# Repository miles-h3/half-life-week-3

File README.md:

# half-life-week-3
MIDI Keyboard PCB Design inspired by Hack Club's guide: an electronic controller that doesn't make sound on its own but sends the data for a computer/synthesizer to generate that audio. Perhaps it can also be programmed to play audio clips?  

FUNCTION:
One's inherent electrical field interacts with the capacitive keys on the pcb and plays a corresponding sound to the key "pressed." Additionally, the switches above the capacitive keys perform the same function though they havae a more physical response to one's touch.

PCB DESIGN:  

3D PCB MODEL:  

## Bill of Materials (BOM)

| Part | Qty | Unit | Total | Vendor |
| :--- | :---: | :---: | :---: | :--- |
| **Custom PCB**<br><sub>connecting all components via electrical signals (?)</sub> | 5 | $0.80 | $4.00 | [JLCPCB](https://jlcpcb.com) |
| **Waveshare ESP32-S3**<br><sub>microcontroller</sub> | 1 | $5.12 | $5.12 | [AliExpress](https://www.aliexpress.com) |
| **switches**<br><sub>interaction</sub> | 10 | $0.10 | $1.00 | [AliExpress](https://www.aliexpress.com) |
| **SK6812 MINI-E Neopixels**<br><sub>glow</sub> | 10 | $0.30 | $3.00 | [AdaFruit](https://www.adafruit.com) |
| **ec11 rotary encoder**<br><sub>interaction</sub> | 1 | $2.14 | $2.14 | [AliExpress](https://www.aliexpress.com) |
| **Tax & shipping**<br><sub>for the whole order</sub> | - | - | $17.42 | - |
| **TOTAL** | - | - | #32.68 | - |

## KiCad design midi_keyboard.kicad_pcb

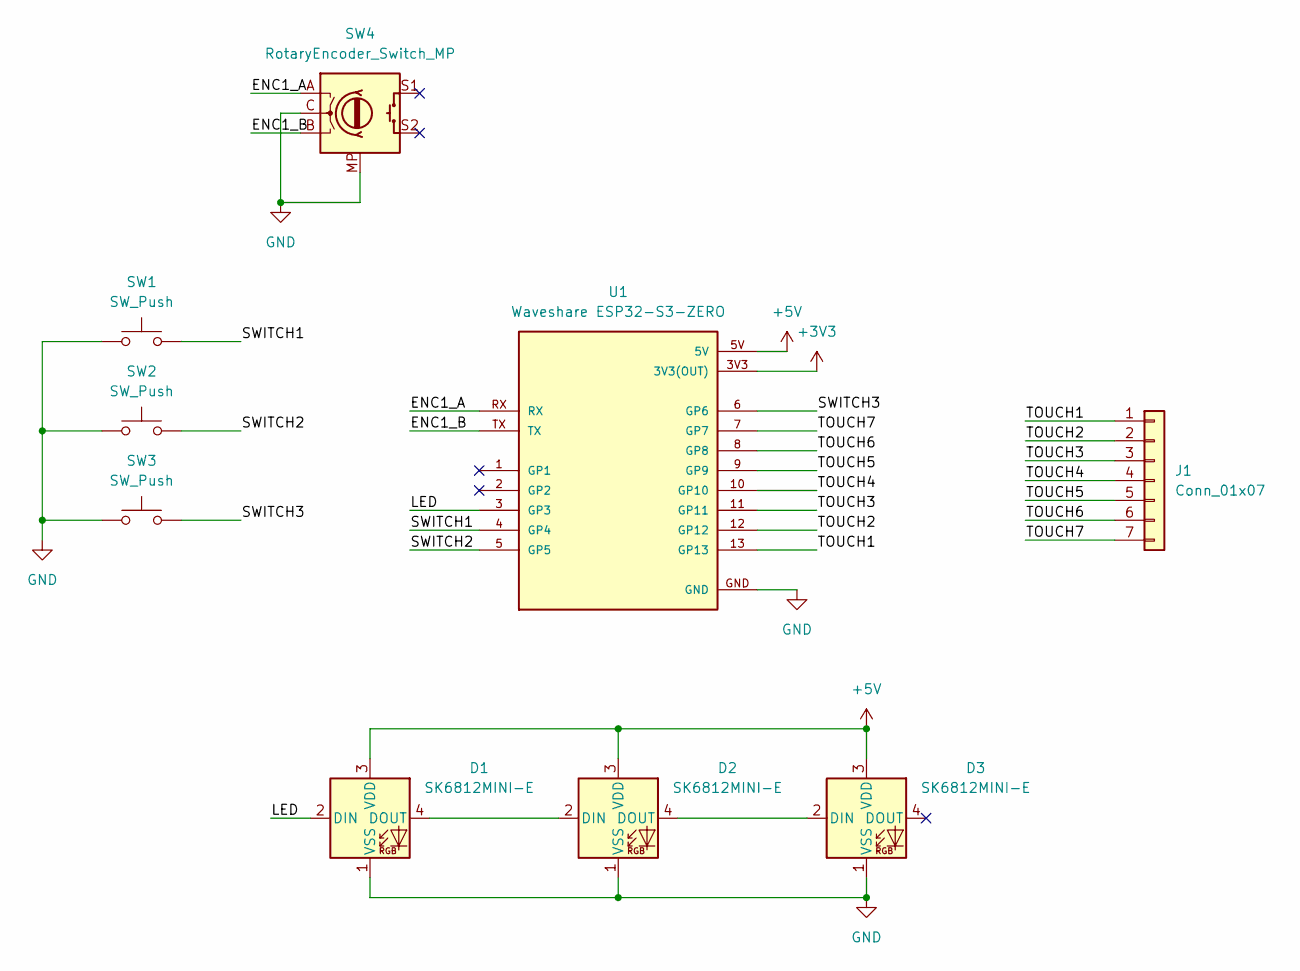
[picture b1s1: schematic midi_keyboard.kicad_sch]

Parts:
D1, D2, D3: SK6812MINI-E; LED_SK6812MINI-E_3.2x2.8mm_P1.5mm_ReverseMount
J1: Conn_01x07; capacitive keys
SW1, SW2, SW3: SW_Push; Kailh Choc Low-Profile Switches
SW4: RotaryEncoder_Switch_MP; RotaryEncoder_Alps_EC11E-Switch_Vertical_H20mm
U1: Waveshare ESP32-S3-ZERO; Waveshare ESP32-S3-Zero; PARTREV NA

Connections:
+3V3: U1.3V3 (3V3(OUT))
+5V: D1.3 (VDD), D2.3 (VDD), D3.3 (VDD), U1.5V
/ENC1_A: SW4.A, U1.RX
/ENC1_B: SW4.B, U1.TX
/LED: D1.2 (DIN), U1.3 (GP3)
/SWITCH1: SW1.2, U1.4 (GP4)
/SWITCH2: SW2.2, U1.5 (GP5)
/SWITCH3: SW3.2, U1.6 (GP6)
/TOUCH1: J1.1, U1.13 (GP13)
/TOUCH2: J1.2, U1.12 (GP12)
/TOUCH3: J1.3, U1.11 (GP11)
/TOUCH4: J1.4, U1.10 (GP10)
/TOUCH5: J1.5, U1.9 (GP9)
/TOUCH6: J1.6, U1.8 (GP8)
/TOUCH7: J1.7, U1.7 (GP7)
GND: D1.1 (VSS), D2.1 (VSS), D3.1 (VSS), SW1.1, SW2.1, SW3.1, SW4.C, SW4.MP, U1.GND
unnamed: D1.4 (DOUT), D2.2 (DIN)
unnamed: D2.4 (DOUT), D3.2 (DIN)

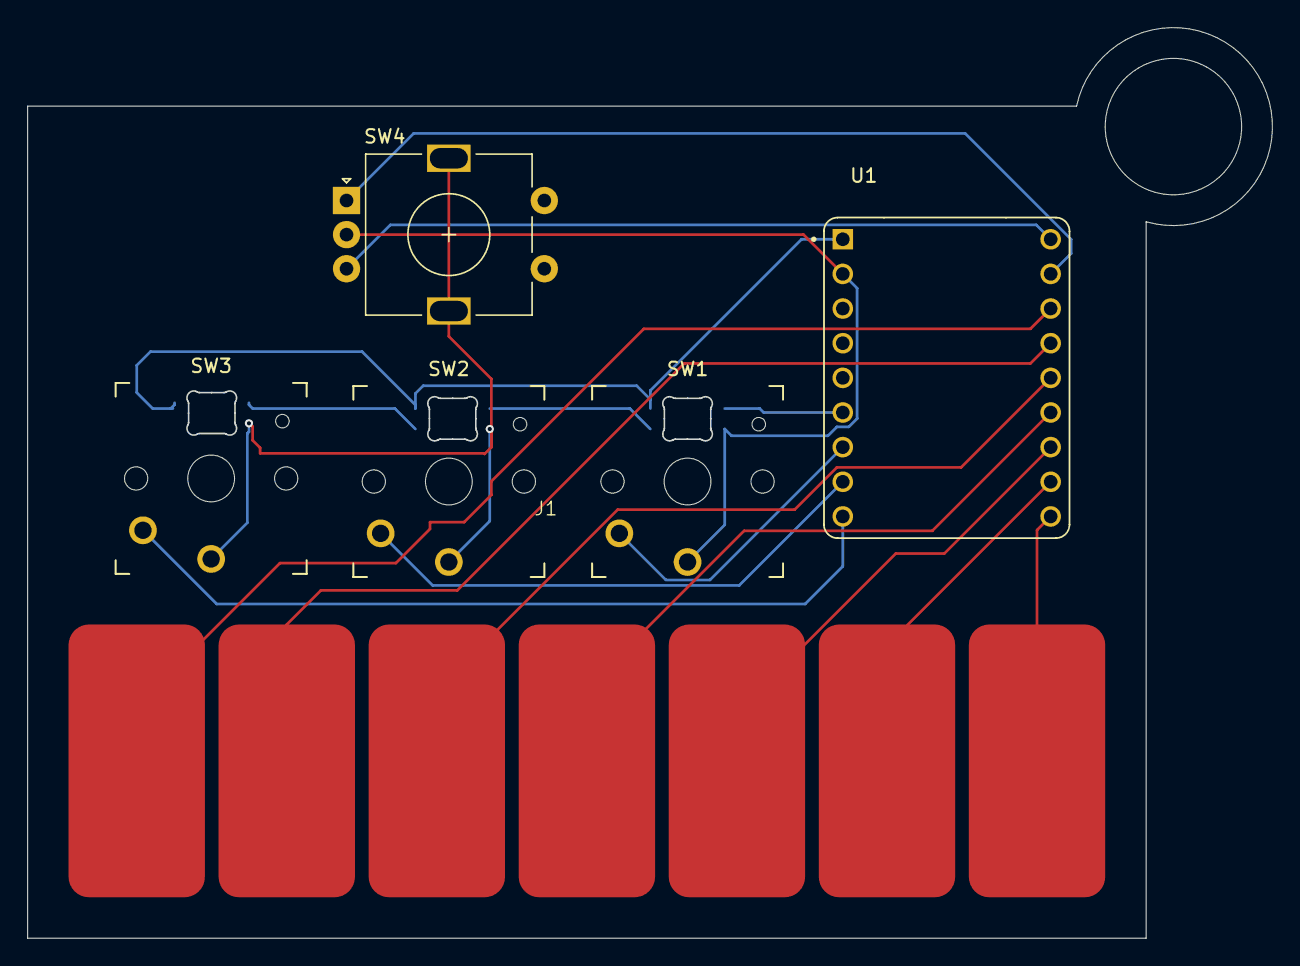
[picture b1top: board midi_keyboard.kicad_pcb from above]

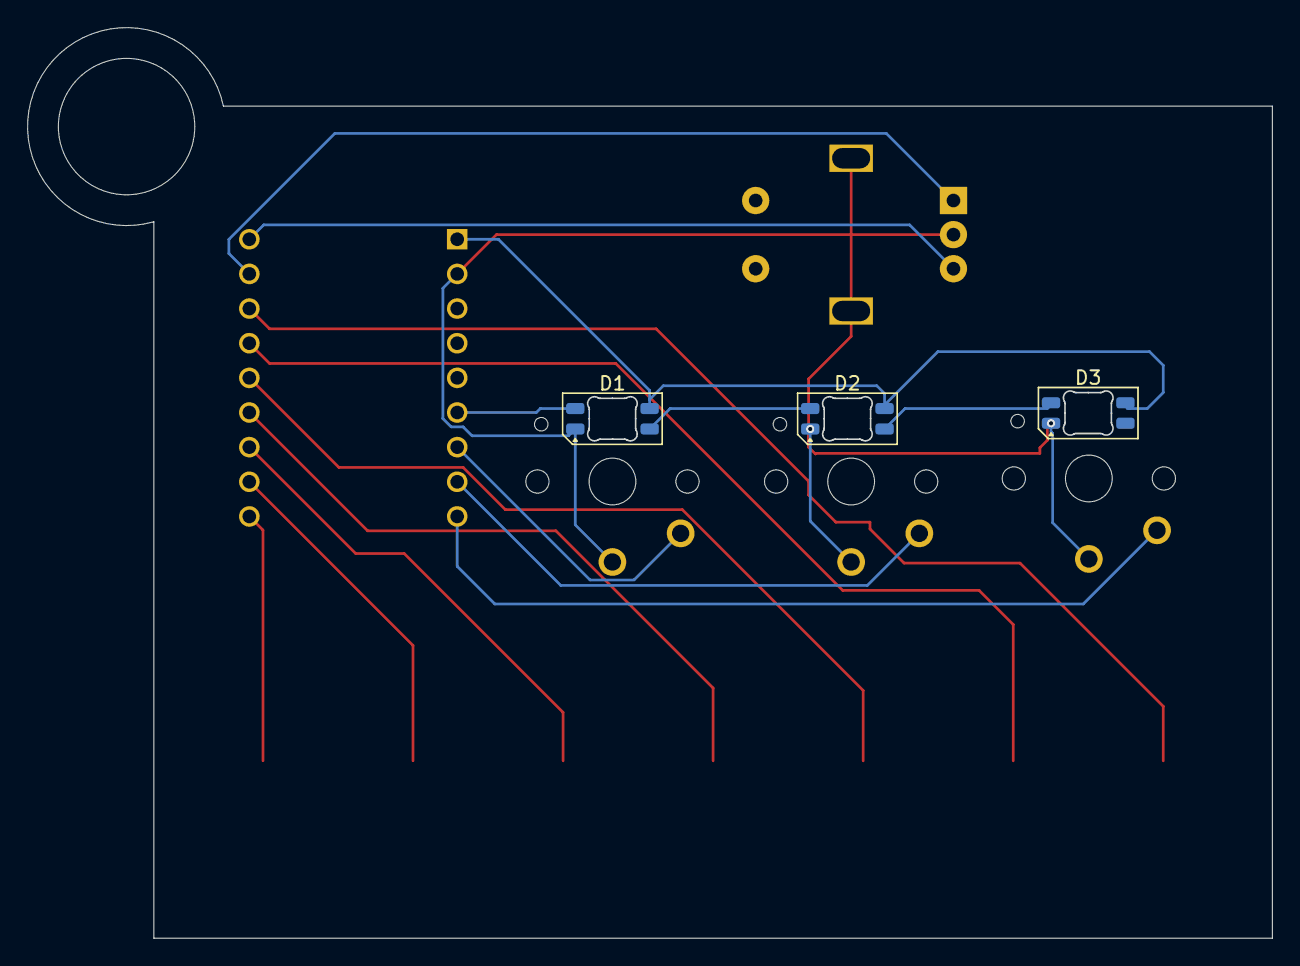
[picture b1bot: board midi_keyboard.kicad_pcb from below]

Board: 2 copper layers, 91.3 x 66.8 mm, 9 parts (3 on the bottom side), 17 nets.
